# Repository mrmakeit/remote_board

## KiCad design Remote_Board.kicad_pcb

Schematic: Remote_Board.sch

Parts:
C1: C4.7u; CP_Elec_3x5.3
D1: LED; LED_0201_0603Metric
J1: Battery Connector; Molex_CLIK-Mate_502382-0270_1x02-1MP_P1.25mm_Vertical
J2, J5: Conn_01x14_Male; PinHeader_1x14_P1.00mm_Vertical
J3: Conn_01x05_Male; PinHeader_1x05_P1.00mm_Vertical
J4: Conn_01x01_Male; PinHeader_1x01_P1.00mm_Vertical
J6: Micro_SD_Card; microSD_HC_Hirose_DM3AT-SF-PEJM5
J7: ROW_INPUT; TE_84952-5_1x05-1MP_P1.0mm_Horizontal
J8: COL_INPUT; TE_84952-5_1x05-1MP_P1.0mm_Horizontal
R1: R2k; R_0201_0603Metric
R2: R470; R_0201_0603Metric
U1: MCP73831-2-OT; SOT-23-5

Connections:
+3V3: J5.2, J6.4; also elsewhere on the board
+BATT: J1.1, J5.1, U1.3 (VBAT)
/Col1: J2.5, J8.1
/Col2: J2.6, J8.2
/Col3: J2.7, J8.3
/Col4: J2.8, J8.4
/Col5: J2.9, J8.5
/LCD_CS: J2.12; also elsewhere on the board
/Row1: J5.7, J7.1
/Row2: J5.8, J7.2
/Row3: J5.9, J7.3
/SD_CS: J2.11, J6.2
/SPI_CLK: J5.14, J6.5
/SPI_MISO: J2.14, J6.7; also elsewhere on the board
/SPI_MOSI: J2.13, J6.3
GND: C1.2, J1.2, J2.1, J6.6, R1.2, U1.2 (VSS); also elsewhere on the board
unnamed: D1.2, R2.1
unnamed: R1.1, U1.5 (PROG)
unnamed: R2.2, U1.1 (STAT)
VBUS: C1.1, D1.1, J4.1, U1.4 (VDD)

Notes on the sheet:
LCD Connectors

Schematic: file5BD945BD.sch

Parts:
U2: 74AHC1G125; SOT-23-5

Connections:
+3V3: U2.5 (VCC); also elsewhere on the board
/LCD Control/LCD_MISO: U2.2
/LCD_CS: U2.1; also elsewhere on the board
/SPI_MISO: U2.4; also elsewhere on the board
GND: U2.3 (GND); also elsewhere on the board

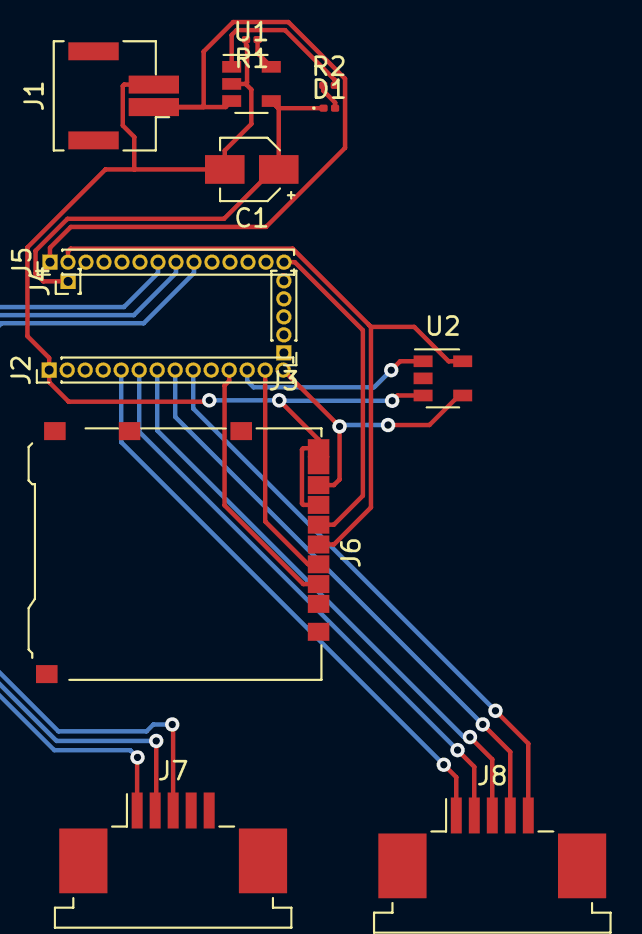
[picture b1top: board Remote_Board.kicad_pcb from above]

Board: 2 copper layers, 14 parts (0 on the bottom side), 20 nets.
